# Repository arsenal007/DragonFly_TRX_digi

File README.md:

# DragonFly_TRX_digi
DragonFly 7Mhz HF transceiver for DIGITAL Modes

Assambly:
 1) Band pass filter
 2) QER Crystal filter
 3) MCU VFO part, first of all RX/TX for RX and TX path power supplay
  3.1 also VFO/BFO is important, using frequency counter to calibrate. BFO use 2µA
  
 4) Q1/Q6 setup current about 20mA
 5) mount 78L06(U13) and mixer, check voltage
 6)

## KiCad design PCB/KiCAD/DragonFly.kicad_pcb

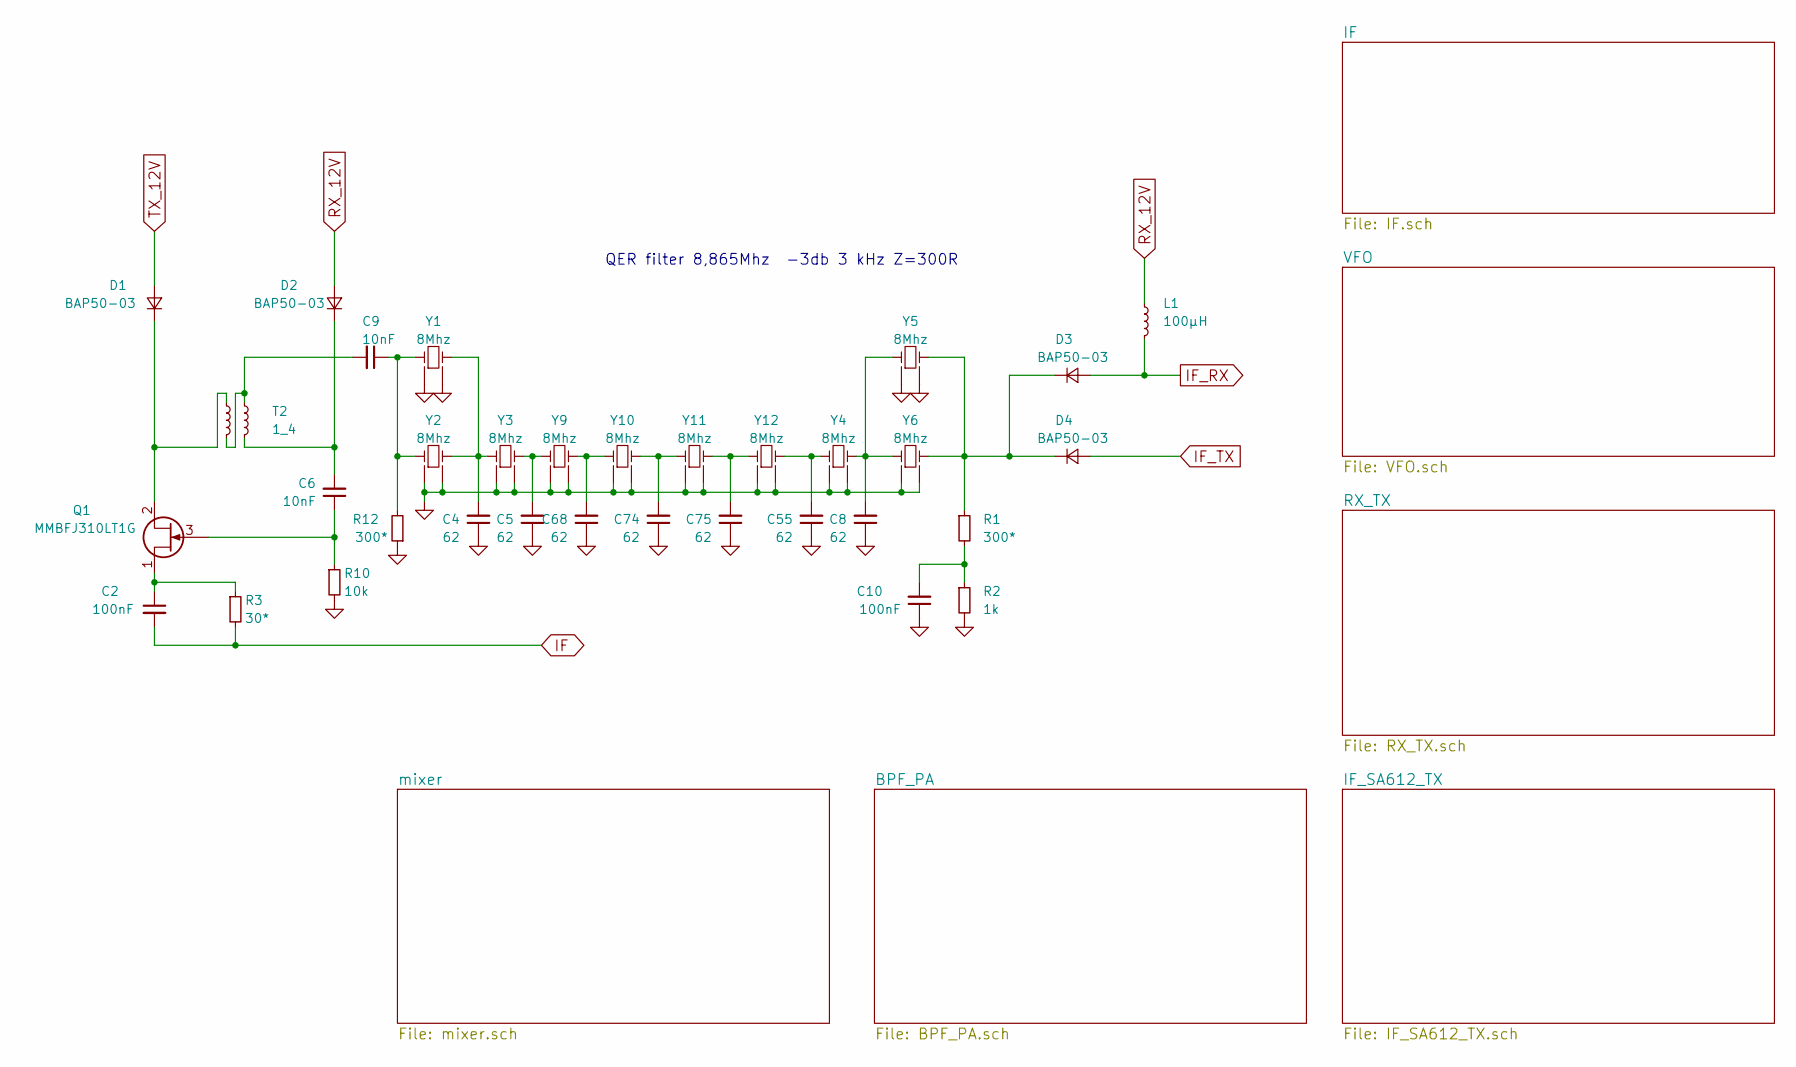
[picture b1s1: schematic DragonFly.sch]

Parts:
C2: 100nF; C_0603_HandSoldering
C4, C5, C8, C55, C68, C74, C75: 62; C_0805
C6, C9: 10nF; C_0603_HandSoldering
C10: 100nF; C_1206_0603
D1, D2, D3, D4: BAP50-03; D_SOD-323_HandSoldering
L1: 100µH; R_Axial_DIN0309_L9.0mm_D3.2mm_P2.54mm_Vertical
Q1: MMBFJ310LT1G; SOT-23
R1, R12: 300*; R_1206_0603
R2: 1k; R_1206_0603
R3: 30*; R_1206_0603
R10: 10k; R_0603_HandSoldering
T2: 1_4; TF14
Y1, Y2, Y3, Y4, Y5, Y6, Y9, Y10, Y11, Y12: 8Mhz; Crystal_HC49-U_Vertical

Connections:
GND: C4.1, C5.1, C8.1, C10.1, C55.1, C68.1, C74.1, C75.1, R2.2, R10.2, R12.1, Y1.3 (GND), Y1.4 (GND), Y2.3 (GND), Y2.4 (GND), Y3.3 (GND), Y3.4 (GND), Y4.3 (GND), Y4.4 (GND), Y5.3 (GND), Y5.4 (GND), Y6.3 (GND), Y6.4 (GND), Y9.3 (GND), Y9.4 (GND), Y10.3 (GND), Y10.4 (GND), Y11.3 (GND), Y11.4 (GND), Y12.3 (GND), Y12.4 (GND); also elsewhere on the board
IF: C2.2, R3.2; also elsewhere on the board
IF_RX: D3.2 (A), L1.2; also elsewhere on the board
IF_TX: D4.2 (A); also elsewhere on the board
unnamed: C2.1, Q1.1 (D), R3.1
unnamed: C4.2, Y1.2, Y2.2, Y3.1
unnamed: C5.2, Y3.2, Y9.1
unnamed: C6.1, Q1.3 (G), R10.1
unnamed: C6.2, D2.1 (K), T2.4
unnamed: C8.2, Y4.2, Y5.1, Y6.1
unnamed: C9.1, R12.2, Y1.1, Y2.1
unnamed: C9.2, T2.2, T2.3
unnamed: C10.2, R1.2, R2.1
unnamed: C55.2, Y4.1, Y12.2
unnamed: C68.2, Y9.2, Y10.1
unnamed: C74.2, Y10.2, Y11.1
unnamed: C75.2, Y11.2, Y12.1
unnamed: D1.1 (K), Q1.2 (S), T2.1
unnamed: D3.1 (K), D4.1 (K), R1.1, Y5.2, Y6.2
RX_12V: D2.2 (A), L1.1; also elsewhere on the board
TX_12V: D1.2 (A); also elsewhere on the board

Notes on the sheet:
QER filter 8,865Mhz -3db 3 kHz Z=300R

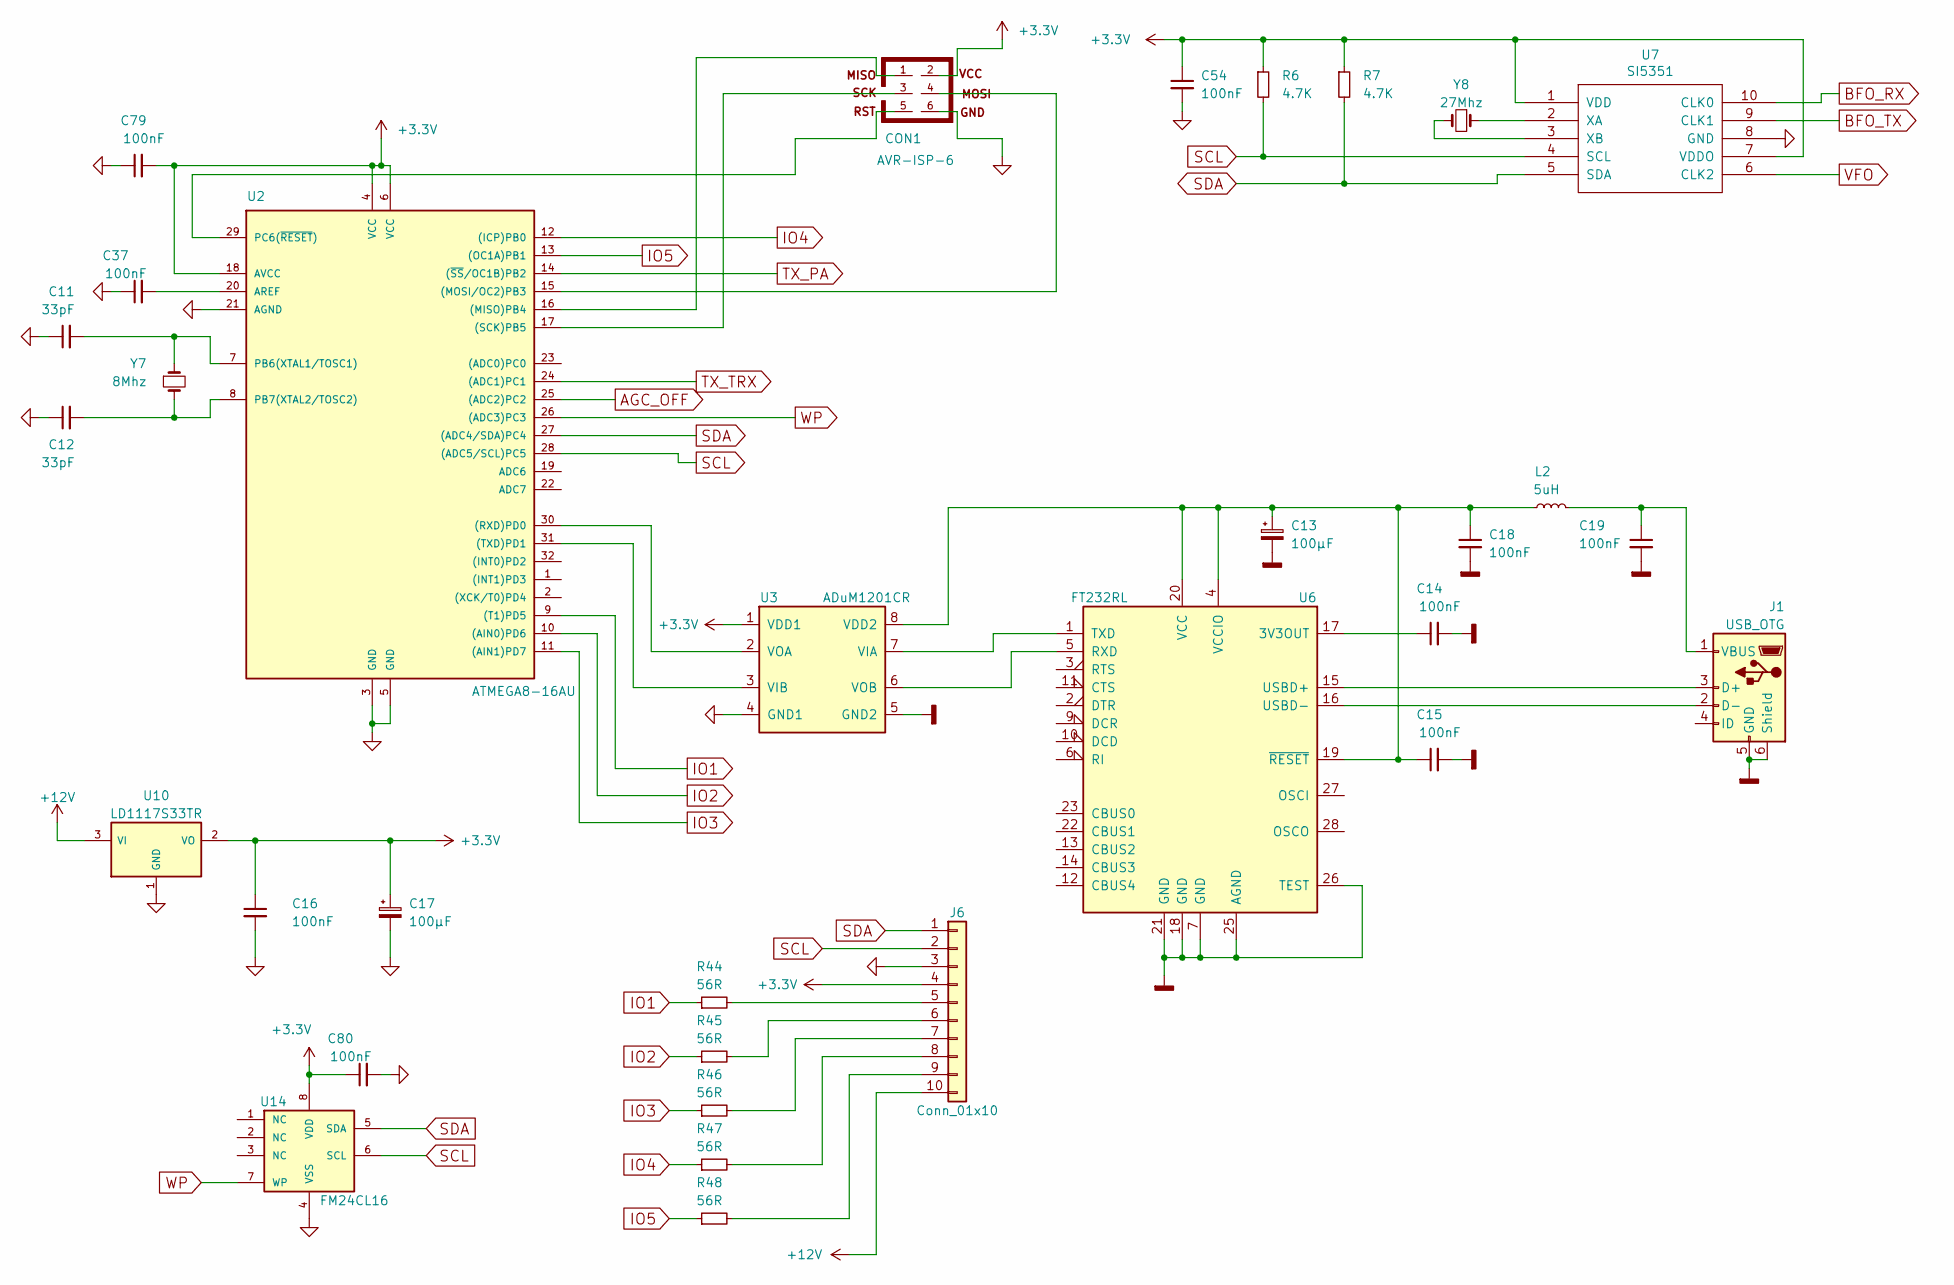
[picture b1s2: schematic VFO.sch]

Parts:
C11, C12: 33pF; C_1206_0603
C13, C17: 100µF; CP_Radial_D6.3mm_P2.50mm
C14, C15, C18, C19: 100nF; C_0603_HandSoldering
C16, C37, C54, C79, C80: 100nF; C_1206_0603
CON1: AVR-ISP-6; Pin_Header_Straight_2x03_Pitch2.54mm
J1: USB_OTG; USB_Mini-B
J6: Conn_01x10; Pin_Header_Straight_1x10_Pitch2.54mm
L2: 5uH; R_Axial_DIN0309_L9.0mm_D3.2mm_P2.54mm_Vertical
R6, R7: 4.7K; R_1206_0603
R44, R45, R46, R47, R48: 56R; R_0603_HandSoldering
U2: ATMEGA8-16AU; TQFP-32_7x7mm_Pitch0.8mm
U3: ADuM1201CR; SOIC-8_3.9x4.9mm_Pitch1.27mm
U6: FT232RL; SSOP-28_5.3x10.2mm_Pitch0.65mm
U7: SI5351; MSOP-10_3x3mm_Pitch0.5mm
U10: LD1117S33TR; SOT-223
U14: FM24CL16; SOIC-8_3.9x4.9mm_Pitch1.27mm
Y7: 8Mhz; Crystal_HC49-4H_Vertical
Y8: 27Mhz; Crystal_SMD_HC49-SD

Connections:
+3V3: C16.1, C17.1, C54.1, C79.2, C80.1, CON1.2, J6.4, R6.1, R7.1, U2.4 (VCC), U2.6 (VCC), U2.18 (AVCC), U3.1 (VDD1), U7.1 (VDD), U7.7 (VDDO), U10.2 (VO), U14.8 (VDD)
+12V: J6.10, U10.3 (VI); also elsewhere on the board
AGC_OFF: U2.25 ((ADC2)PC2); also elsewhere on the board
BFO_RX: U7.10 (CLK0); also elsewhere on the board
BFO_TX: U7.9 (CLK1); also elsewhere on the board
GND: C11.1, C12.1, C16.2, C17.2, C37.1, C54.2, C79.1, C80.2, CON1.6, J6.3, U2.3 (GND), U2.5 (GND), U2.21 (AGND), U3.4 (GND1), U7.8 (GND), U10.1 (GND), U14.4 (VSS); also elsewhere on the board
GNDD: C13.2, C14.2, C15.2, C18.2, C19.2, J1.5 (GND), J1.6 (Shield), U3.5 (GND2), U6.7 (GND), U6.18 (GND), U6.21 (GND), U6.25 (AGND), U6.26 (TEST)
IO1: R44.1, U2.9 ((T1)PD5)
IO2: R45.1, U2.10 ((AIN0)PD6)
IO3: R46.1, U2.11 ((AIN1)PD7)
IO4: R47.1, U2.12 ((ICP)PB0)
IO5: R48.1, U2.13 ((OC1A)PB1)
unnamed: C11.2, U2.7 (PB6(XTAL1/TOSC1)), Y7.1
unnamed: C12.2, U2.8 (PB7(XTAL2/TOSC2)), Y7.2
unnamed: C13.1, C15.1, C18.1, L2.1, U3.8 (VDD2), U6.4 (VCCIO), U6.19 (~RESET~), U6.20 (VCC)
unnamed: C14.1, U6.17 (3V3OUT)
unnamed: C19.1, J1.1 (VBUS), L2.2
unnamed: C37.2, U2.20 (AREF)
unnamed: CON1.1, U2.16 ((MISO)PB4)
unnamed: CON1.3, U2.17 ((SCK)PB5)
unnamed: CON1.4, U2.15 ((MOSI/OC2)PB3)
unnamed: CON1.5, U2.29 (PC6(~RESET~))
unnamed: J1.2 (D-), U6.16 (USBD-)
unnamed: J1.3 (D+), U6.15 (USBD+)
unnamed: J6.5, R44.2
unnamed: J6.6, R45.2
unnamed: J6.7, R46.2
unnamed: J6.8, R47.2
unnamed: J6.9, R48.2
unnamed: U2.30 ((RXD)PD0), U3.2 (VOA)
unnamed: U2.31 ((TXD)PD1), U3.3 (VIB)
unnamed: U3.6 (VOB), U6.5 (RXD)
unnamed: U3.7 (VIA), U6.1 (TXD)
unnamed: U7.2 (XA), Y8.1
unnamed: U7.3 (XB), Y8.2
SCL: J6.2, R6.2, U2.28 ((ADC5/SCL)PC5), U7.4 (SCL), U14.6 (SCL)
SDA: J6.1, R7.2, U2.27 ((ADC4/SDA)PC4), U7.5 (SDA), U14.5 (SDA)
TX_PA: U2.14 ((~SS~/OC1B)PB2); also elsewhere on the board
TX_TRX: U2.24 ((ADC1)PC1); also elsewhere on the board
VFO: U7.6 (CLK2); also elsewhere on the board
WP: U2.26 ((ADC3)PC3), U14.7 (WP)

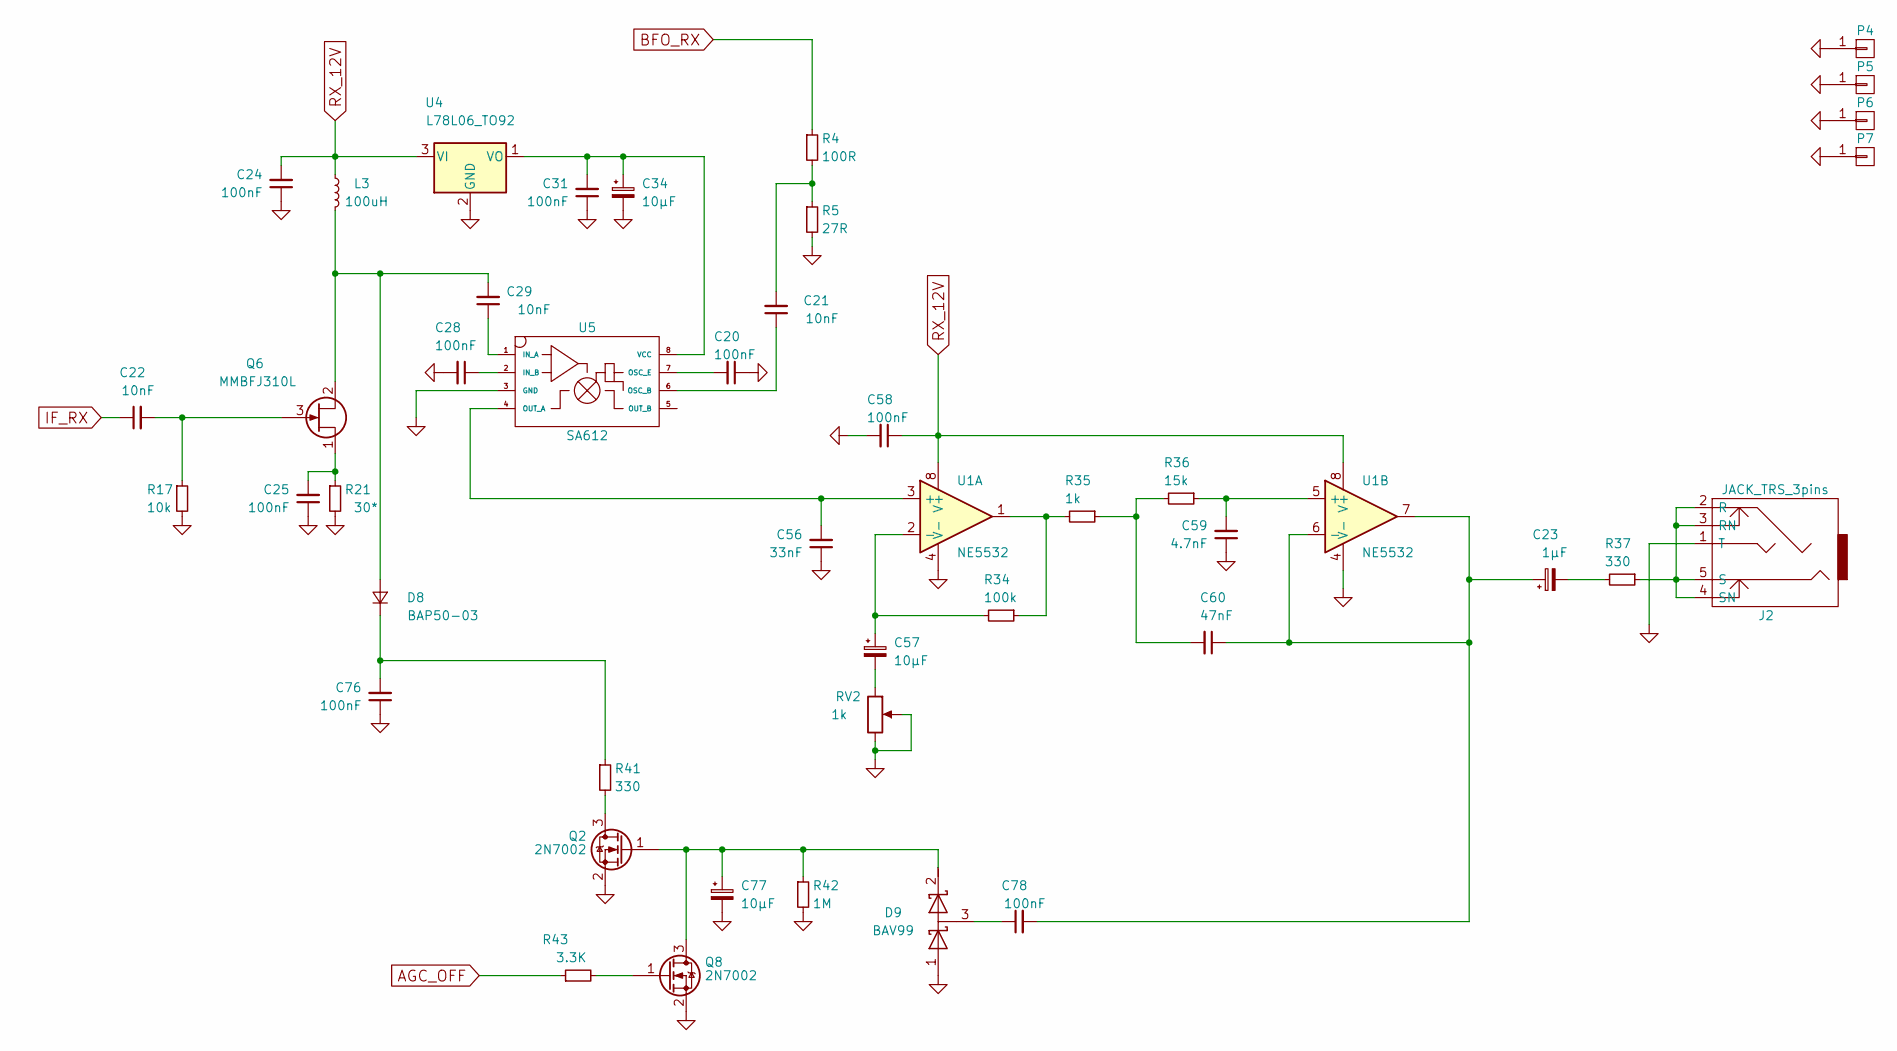
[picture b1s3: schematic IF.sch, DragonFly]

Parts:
C20, C24, C25, C28, C31, C58, C76, C78: 100nF; C_1206_0603
C21, C22, C29: 10nF; C_0603_HandSoldering
C23: 1µF; CP_Radial_D4.0mm_P2.00mm
C34, C57, C77: 10µF; CP_Radial_D4.0mm_P2.00mm
C56: 33nF; C_1206_0603
C59: 4.7nF; C_0603_HandSoldering
C60: 47nF; C_1206_0603
D8: BAP50-03; D_SOD-323_HandSoldering
D9: BAV99; SOT-23
J2: JACK_TRS_3pins; audio_jack_3_5mm_PJ307
L3: 100uH; R_Axial_DIN0309_L9.0mm_D3.2mm_P2.54mm_Vertical
P4, P5, P6, P7: CONN_01X01; MountingHole_3.2mm_M3_DIN965_Pad
Q2, Q8: 2N7002; SOT-23
Q6: MMBFJ310L; SOT-23
R4: 100R; R_1206_0603
R5: 27R; R_1206_0603
R17: 10k; R_1206_0603
R21: 30*; R_1206_0603
R34: 100k; R_1206_0603
R35: 1k; R_0603_HandSoldering
R36: 15k; R_0603_HandSoldering
R37, R41: 330; R_1206_0603
R42: 1M; R_1206_0603
R43: 3.3K; R_1206_0603
RV2: 1k; Potentiometer_Trimmer_Piher_PT-6v_Horizontal
U1: NE5532; SOIC-8_3.9x4.9mm_Pitch1.27mm
U4: L78L06_TO92; TO-92_Molded_Wide_Oval
U5: SA612; SOIC-8_3.9x4.9mm_Pitch1.27mm

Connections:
AGC_OFF: R43.1; also elsewhere on the board
BFO_RX: R4.1; also elsewhere on the board
GND: C20.1, C24.1, C25.1, C28.2, C31.1, C34.2, C56.1, C58.2, C59.1, C76.1, C77.2, D9.1 (A), J2.1 (T), P4.1, P5.1, P6.1, P7.1, Q2.2 (S), Q8.2 (S), R5.2, R17.2, R21.2, R42.2, RV2.2, RV2.3, U1.4 (V-), U4.2 (GND), U5.3 (GND); also elsewhere on the board
IF_RX: C22.1; also elsewhere on the board
unnamed: C20.2, U5.7 (OSC_E)
unnamed: C21.1, U5.6 (OSC_B)
unnamed: C21.2, R4.2, R5.1
unnamed: C22.2, Q6.3 (G), R17.1
unnamed: C23.1, C60.1, C78.2, U1.6 (-), U1.7
unnamed: C23.2, R37.2
unnamed: C25.2, Q6.1 (D), R21.1
unnamed: C28.1, U5.2 (IN_B)
unnamed: C29.1, U5.1 (IN_A)
unnamed: C29.2, D8.2 (A), L3.2, Q6.2 (S)
unnamed: C31.2, C34.1, U4.1 (VO), U5.8 (VCC)
unnamed: C56.2, U1.3 (+), U5.4 (OUT_A)
unnamed: C57.1, R34.2, U1.2 (-)
unnamed: C57.2, RV2.1
unnamed: C59.2, R36.1, U1.5 (+)
unnamed: C60.2, R35.1, R36.2
unnamed: C76.2, D8.1 (K), R41.1
unnamed: C77.1, D9.2 (K), Q2.1 (G), Q8.3 (D), R42.1
unnamed: C78.1, D9.3 (common)
unnamed: J2.2 (R), J2.3 (RN), J2.4 (SN), J2.5 (S), R37.1
unnamed: Q2.3 (D), R41.2
unnamed: Q8.1 (G), R43.2
unnamed: R34.1, R35.2, U1.1
RX_12V: C24.2, C58.1, L3.1, U1.8 (V+), U4.3 (VI); also elsewhere on the board

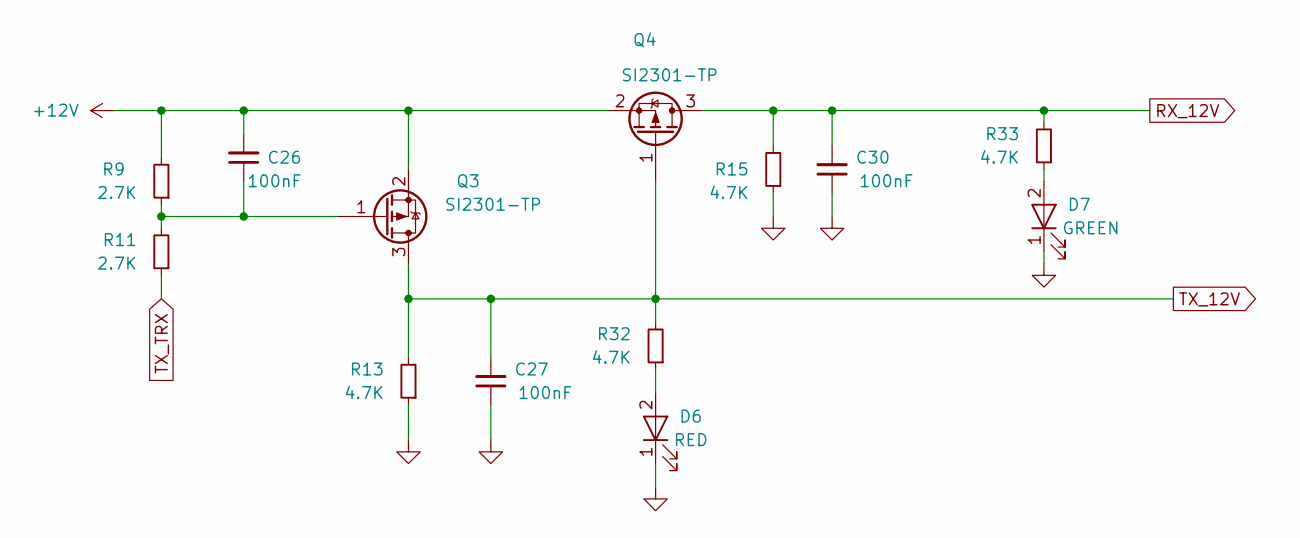
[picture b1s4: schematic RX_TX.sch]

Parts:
C26, C27, C30: 100nF; C_1206_0603
D6: RED; LED_D3.0mm_Horizontal_O3.81mm_Z10.0mm
D7: GREEN; LED_D3.0mm_Horizontal_O3.81mm_Z10.0mm
Q3, Q4: SI2301-TP; SOT-23
R9, R11: 2.7K; R_1206_0603
R13, R15, R32, R33: 4.7K; R_1206_0603

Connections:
+12V: C26.2, Q3.2 (S), Q4.2 (S), R9.2; also elsewhere on the board
GND: C27.1, C30.1, D6.1 (K), D7.1 (K), R13.1, R15.1; also elsewhere on the board
unnamed: C26.1, Q3.1 (G), R9.1, R11.2
unnamed: D6.2 (A), R32.1
unnamed: D7.2 (A), R33.1
RX_12V: C30.2, Q4.3 (D), R15.2, R33.2; also elsewhere on the board
TX_12V: C27.2, Q3.3 (D), Q4.1 (G), R13.2, R32.2; also elsewhere on the board
TX_TRX: R11.1; also elsewhere on the board

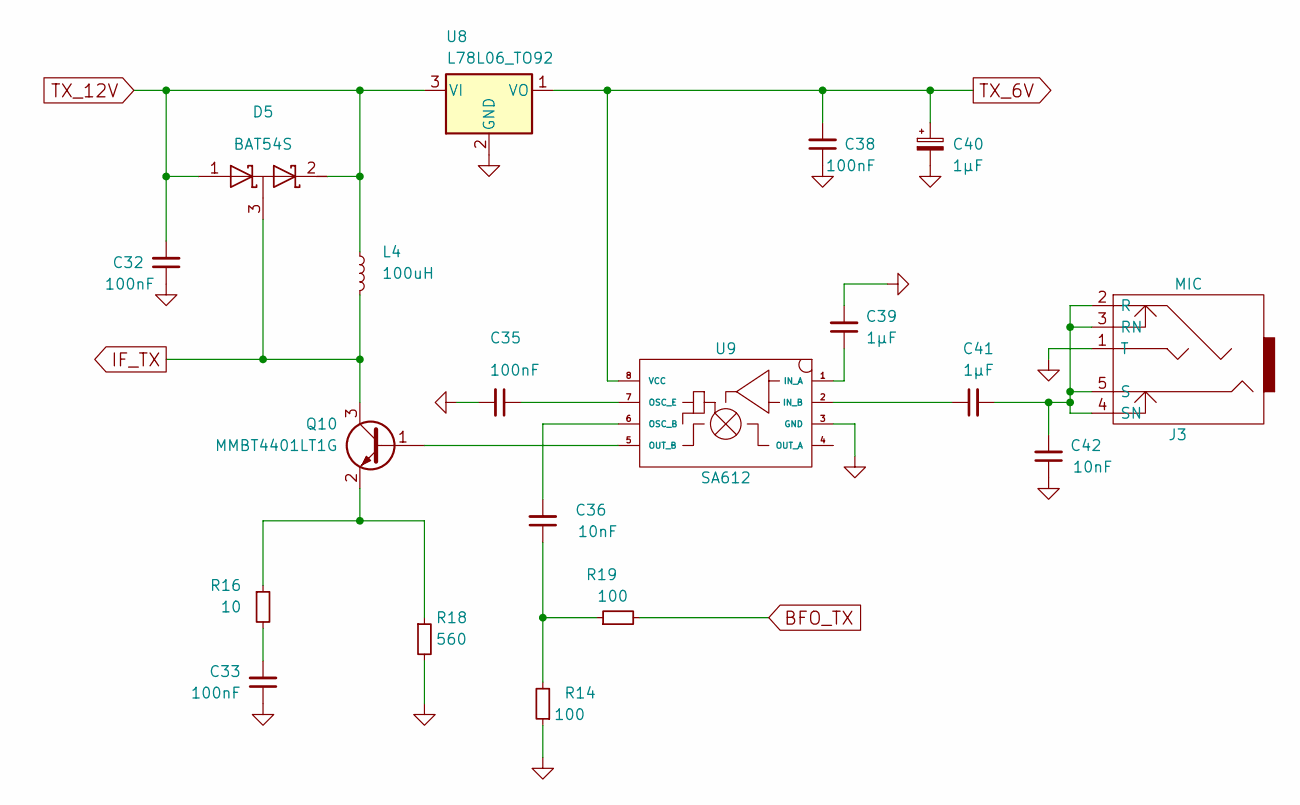
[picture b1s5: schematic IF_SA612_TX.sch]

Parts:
C32, C33, C35, C38: 100nF; C_1206_0603
C36, C42: 10nF; C_0603_HandSoldering
C39, C41: 1µF; C_1206_0603
C40: 1µF; CP_Radial_D4.0mm_P2.00mm
D5: BAT54S; SOT-23
J3: MIC; audio_jack_3_5mm_PJ307
L4: 100uH; R_Axial_DIN0309_L9.0mm_D3.2mm_P2.54mm_Vertical
Q10: MMBT4401LT1G; SOT-23
R14, R19: 100; R_1206_0603
R16: 10; R_1206_0603
R18: 560; R_1206_0603
U8: L78L06_TO92; TO-92_Molded_Wide_Oval
U9: SA612; SOIC-8_3.9x4.9mm_Pitch1.27mm

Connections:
BFO_TX: R19.2; also elsewhere on the board
GND: C32.1, C33.1, C35.2, C38.1, C39.2, C40.2, C42.1, J3.1 (T), R14.1, R18.2, U8.2 (GND), U9.3 (GND); also elsewhere on the board
IF_TX: D5.3 (common), L4.2, Q10.3 (C); also elsewhere on the board
unnamed: C33.2, R16.2
unnamed: C35.1, U9.7 (OSC_E)
unnamed: C36.1, R14.2, R19.1
unnamed: C36.2, U9.6 (OSC_B)
unnamed: C39.1, U9.1 (IN_A)
unnamed: C41.1, U9.2 (IN_B)
unnamed: C41.2, C42.2, J3.2 (R), J3.3 (RN), J3.4 (SN), J3.5 (S)
unnamed: Q10.1 (B), U9.5 (OUT_B)
unnamed: Q10.2 (E), R16.1, R18.1
TX_6V: C38.2, C40.1, U8.1 (VO), U9.8 (VCC); also elsewhere on the board
TX_12V: C32.2, D5.1 (A), D5.2 (K), L4.1, U8.3 (VI); also elsewhere on the board

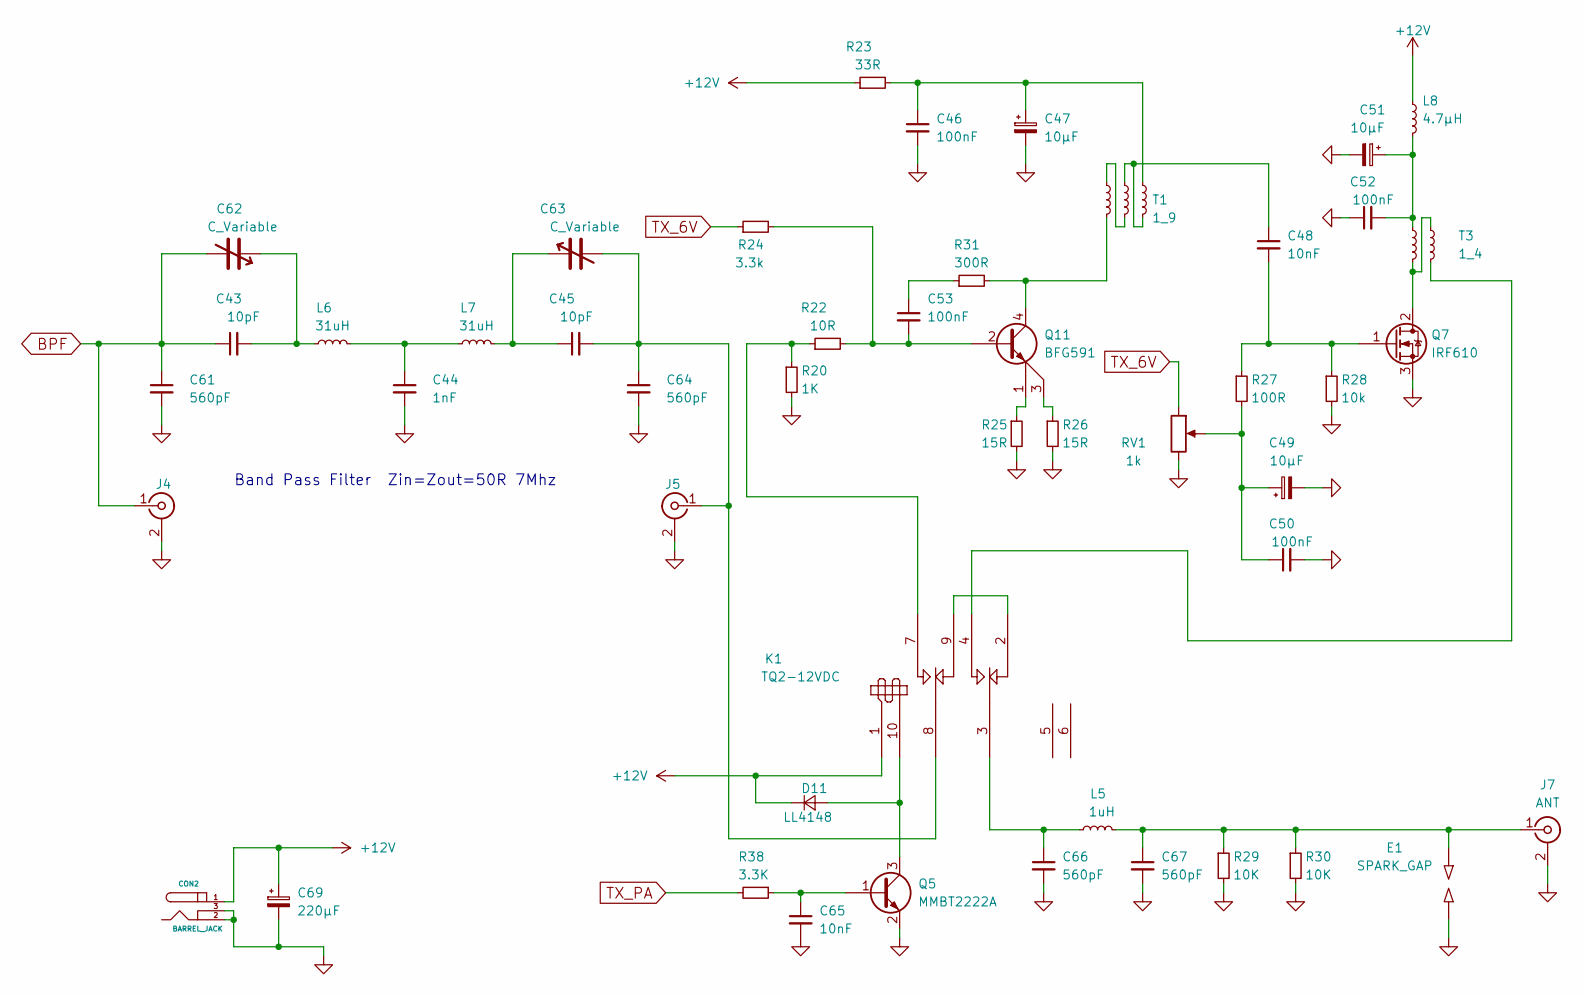
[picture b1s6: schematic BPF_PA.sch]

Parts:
C43, C45: 10pF; C_1206_0603
C44: 1nF; C_1206_0603
C46, C50, C52, C53: 100nF; C_1206_0603
C47, C49, C51: 10µF; CP_Radial_D4.0mm_P2.00mm
C48, C65: 10nF; C_0603_HandSoldering
C61, C64, C66, C67: 560pF; C_1206_0603
C62, C63: C_Variable; C_Trimmer_Voltronics_JZ
C69: 220µF; CP_Radial_D6.3mm_P2.50mm
CON2: BARREL_JACK
D11: LL4148; MiniMELF_Standard
E1: SPARK_GAP; Resistor_Vertical_RM5mm
J4, J5: Conn_Coaxial; U.FL_Molex_MCRF_73412-0110_Vertical
J7: ANT; SMA_THT_Jack_Straight
K1: TQ2-12VDC; Relay_DPDT_FRT5
L5: 1uH; Choke_Toroid_5x10mm_Vertical
L6, L7: 31uH; Choke_Toroid_5x10mm_Vertical
L8: 4.7µH; Choke_CD54
Q5: MMBT2222A; SOT-23
Q7: IRF610; TO-220_Neutral123_Horizontal_LargePads_BigHole
Q11: BFG591; SOT-223
R20: 1K; R_1206_0603
R22: 10R; R_1206_0603
R23: 33R; R_2512
R24: 3.3k; R_1206_0603
R25, R26: 15R; R_1206_0603
R27: 100R; R_1206_0603
R28: 10k; R_1206_0603
R29, R30: 10K; R_1206_0603
R31: 300R; R_1206_0603
R38: 3.3K; R_1206_0603
RV1: 1k; Potentiometer_Trimmer_Bourns_3296W
T1: 1_9; HF12
T3: 1_4; TRANSF1_4

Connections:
+12V: C69.1, CON2.1, D11.1 (K), K1.1 (+), L8.1, R23.1; also elsewhere on the board
BPF: C43.1, C61.1, C62.2, J4.1 (In); also elsewhere on the board
GND: C44.2, C46.2, C47.2, C49.2, C50.2, C51.2, C52.1, C61.2, C64.2, C65.2, C66.2, C67.2, C69.2, CON2.2, CON2.3, E1.2, J4.2 (Ext), J5.2 (Ext), J7.2 (Ext), Q5.2 (E), Q7.3 (S), R20.2, R25.2, R26.2, R28.2, R29.2, R30.2, RV1.3; also elsewhere on the board
unnamed: C43.2, C62.1, L6.1
unnamed: C44.1, L6.2, L7.1
unnamed: C45.1, C63.1, L7.2
unnamed: C45.2, C63.2, C64.1, J5.1 (In), K1.8 (C1)
unnamed: C46.1, C47.1, R23.2, T1.6
unnamed: C48.1, T1.4, T1.5
unnamed: C48.2, Q7.1 (G), R27.1, R28.1
unnamed: C49.1, C50.1, R27.2, RV1.2
unnamed: C51.1, C52.2, L8.2, T3.1
unnamed: C53.1, R31.1
unnamed: C53.2, Q11.2 (B), R22.2, R24.2
unnamed: C65.1, Q5.1 (B), R38.1
unnamed: C66.1, K1.3 (C2), L5.1
unnamed: C67.1, E1.1, J7.1 (In), L5.2, R29.1, R30.1
unnamed: D11.2 (A), K1.10 (-), Q5.3 (C)
unnamed: K1.2 (R2), K1.9 (R1)
unnamed: K1.4 (T2), T3.4
unnamed: K1.7 (T1), R20.1, R22.1
unnamed: Q7.2 (D), T3.2, T3.3
unnamed: Q11.1 (E), R25.1
unnamed: Q11.3 (E), R26.1
unnamed: Q11.4 (C), R31.2, T1.1
unnamed: T1.2, T1.3
TX_6V: R24.1, RV1.1; also elsewhere on the board
TX_PA: R38.2; also elsewhere on the board

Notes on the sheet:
Band Pass Filter Zin=Zout=50R 7Mhz

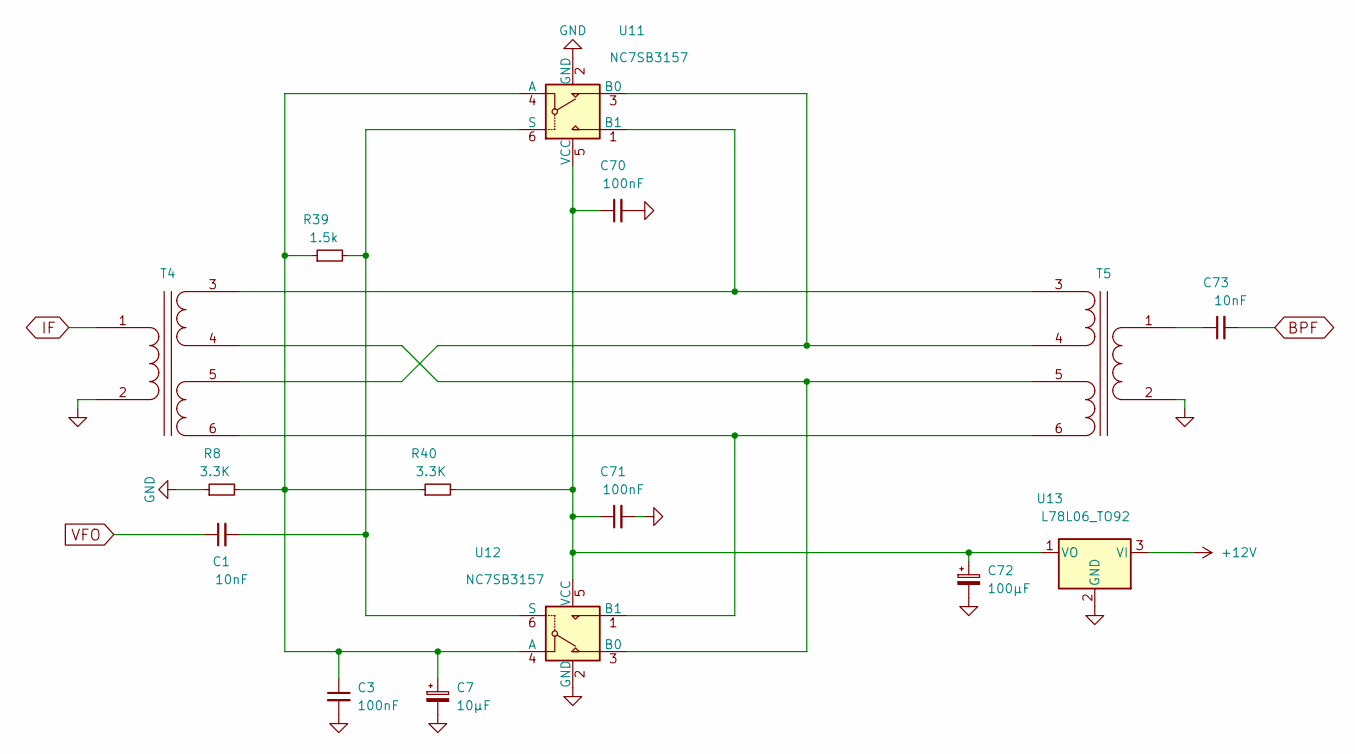
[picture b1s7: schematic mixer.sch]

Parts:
C1, C73: 10nF; C_0603_HandSoldering
C3, C70, C71: 100nF; C_1206_0603
C7: 10µF; CP_Radial_D4.0mm_P2.00mm
C72: 100µF; CP_Radial_D6.3mm_P2.50mm
R8, R40: 3.3K; R_1206_0603
R39: 1.5k; R_1206_0603
T4, T5: Transformer_1P_2S; HF12
U11, U12: NC7SB3157; SOT-23-6
U13: L78L06_TO92; TO-92_Molded_Wide_Oval

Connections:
+12V: U13.3 (VI); also elsewhere on the board
BPF: C73.2; also elsewhere on the board
GND: C3.2, C7.2, C70.2, C71.2, C72.2, R8.1, T4.2 (AB), T5.2 (AB), U11.2 (GND), U12.2 (GND), U13.2 (GND); also elsewhere on the board
IF: T4.1 (AA); also elsewhere on the board
unnamed: C1.2, R39.2, U11.6 (S), U12.6 (S)
unnamed: C3.1, C7.1, R8.2, R39.1, R40.1, U11.4 (A), U12.4 (A)
unnamed: C70.1, C71.1, C72.1, R40.2, U11.5 (VCC), U12.5 (VCC), U13.1 (VO)
unnamed: C73.1, T5.1 (AA)
unnamed: T4.3 (SA), T5.3 (SA), U11.1 (B1)
unnamed: T4.4 (SB), T5.5 (SC), U12.3 (B0)
unnamed: T4.5 (SC), T5.4 (SB), U11.3 (B0)
unnamed: T4.6 (SD), T5.6 (SD), U12.1 (B1)
VFO: C1.1; also elsewhere on the board

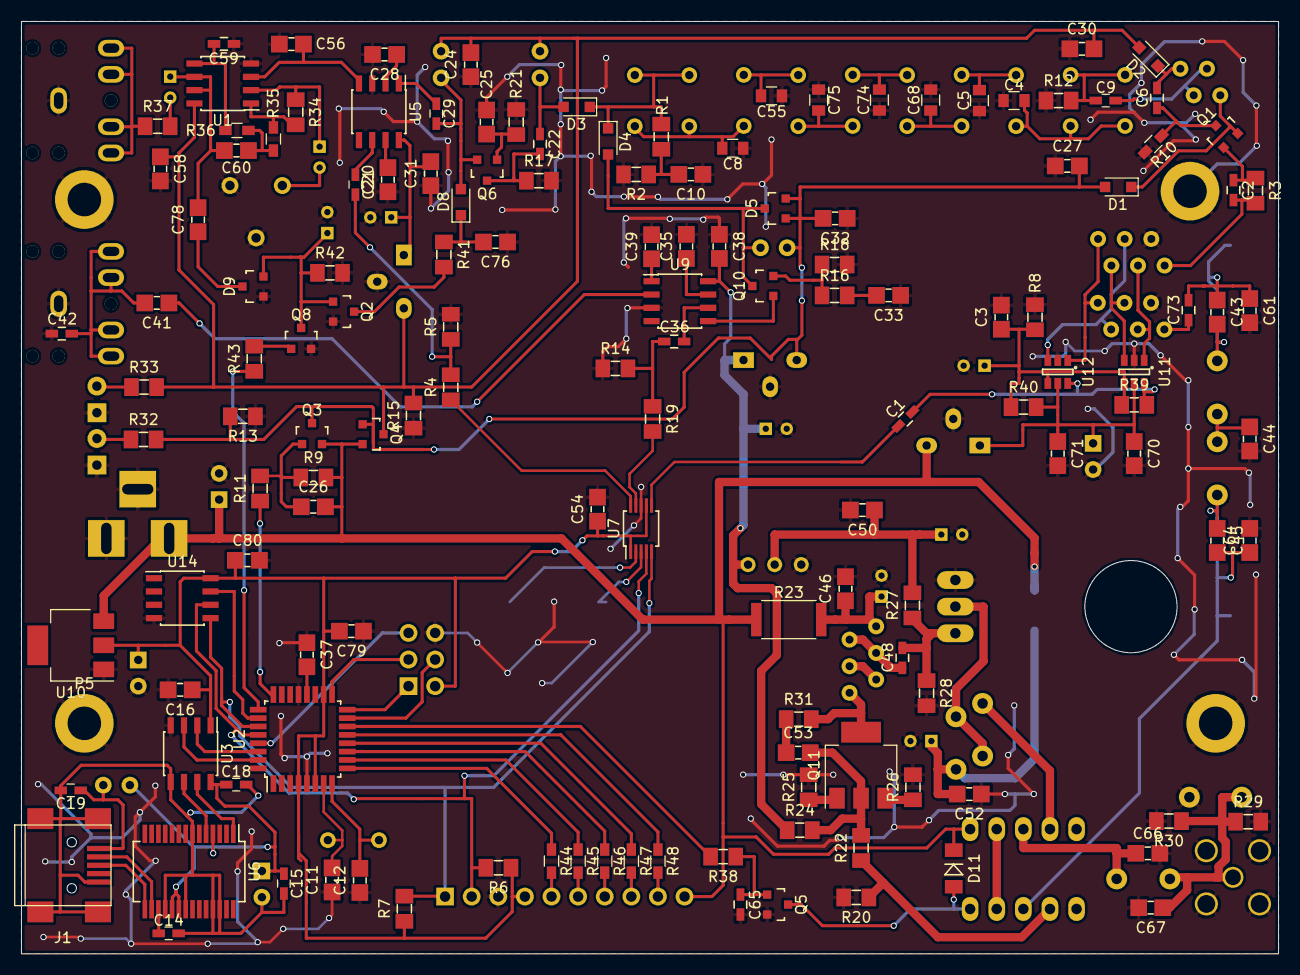
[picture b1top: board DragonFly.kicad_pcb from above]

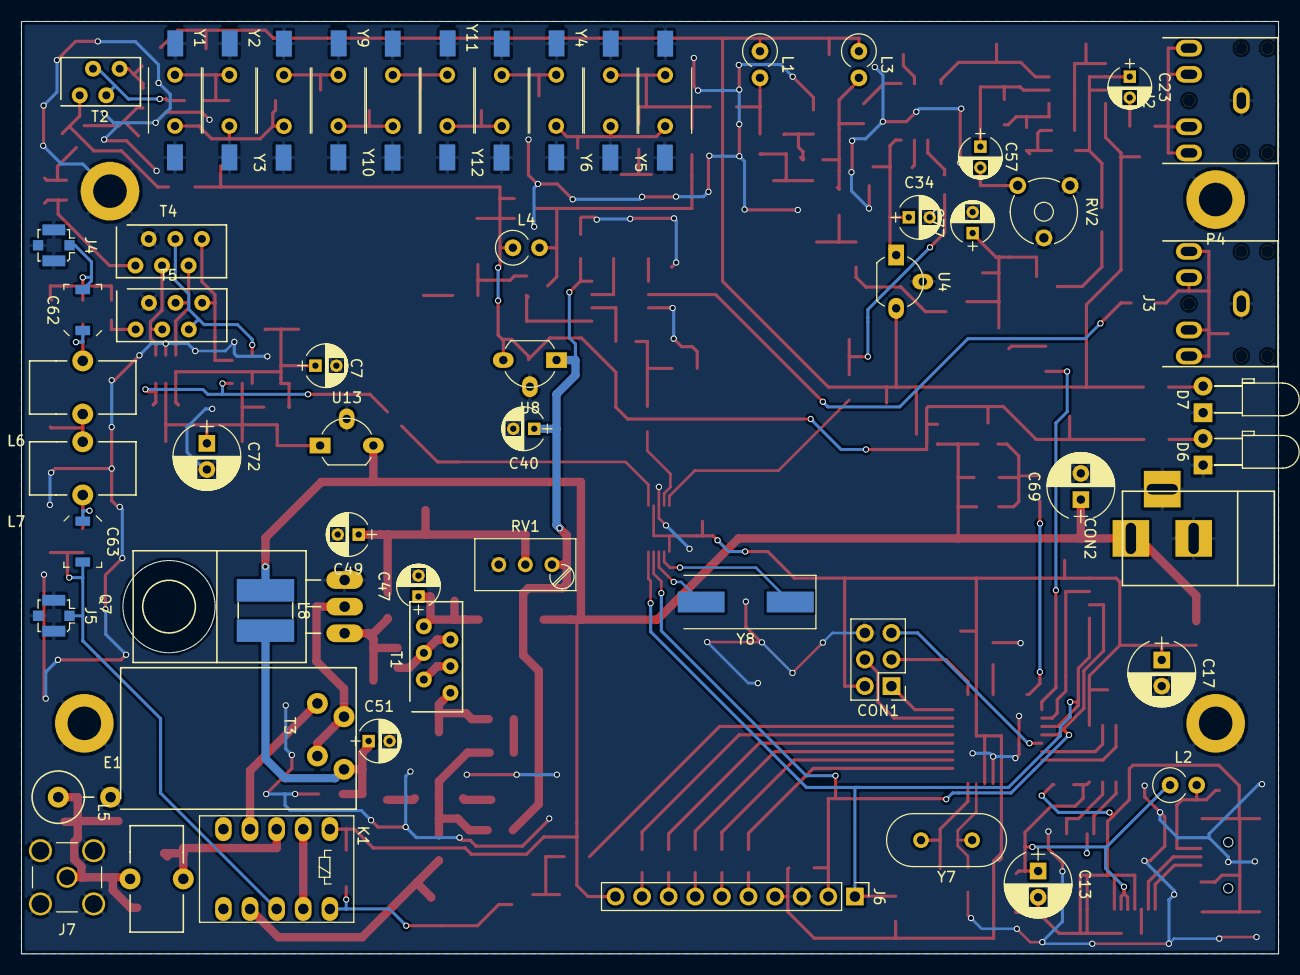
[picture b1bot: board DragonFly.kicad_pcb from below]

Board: 2 copper layers, 120.0 x 89.0 mm, 204 parts (60 on the bottom side), 129 nets.

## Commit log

2021-08-23 diode mixer on discrete components, begin move to DragonFly libs
2021-08-23 begin BPF
2021-08-23 PCB read works, layout BPF
2021-08-24 PCB progress, QER filter place, PA place
2021-08-24 PCB progress, IF TX, IF RX, PowerSupply Jack
2021-08-25 PCB progress, add digital pin interface, polygon GND, some layout
2021-08-28 PCB progress, fix MMBFJ310 error
2021-08-29 UR5FFR Mixer FSA3157
2021-08-30 mixer schema is done, pcb progress, fix 78l06 issue
2021-08-31 PCB home
2021-08-31 denser layout
2021-08-31 add AGC circuit
2021-09-01 add FM24CL16,PCB progress
2021-09-07 PCB v1.0
2021-09-08 PCB production
